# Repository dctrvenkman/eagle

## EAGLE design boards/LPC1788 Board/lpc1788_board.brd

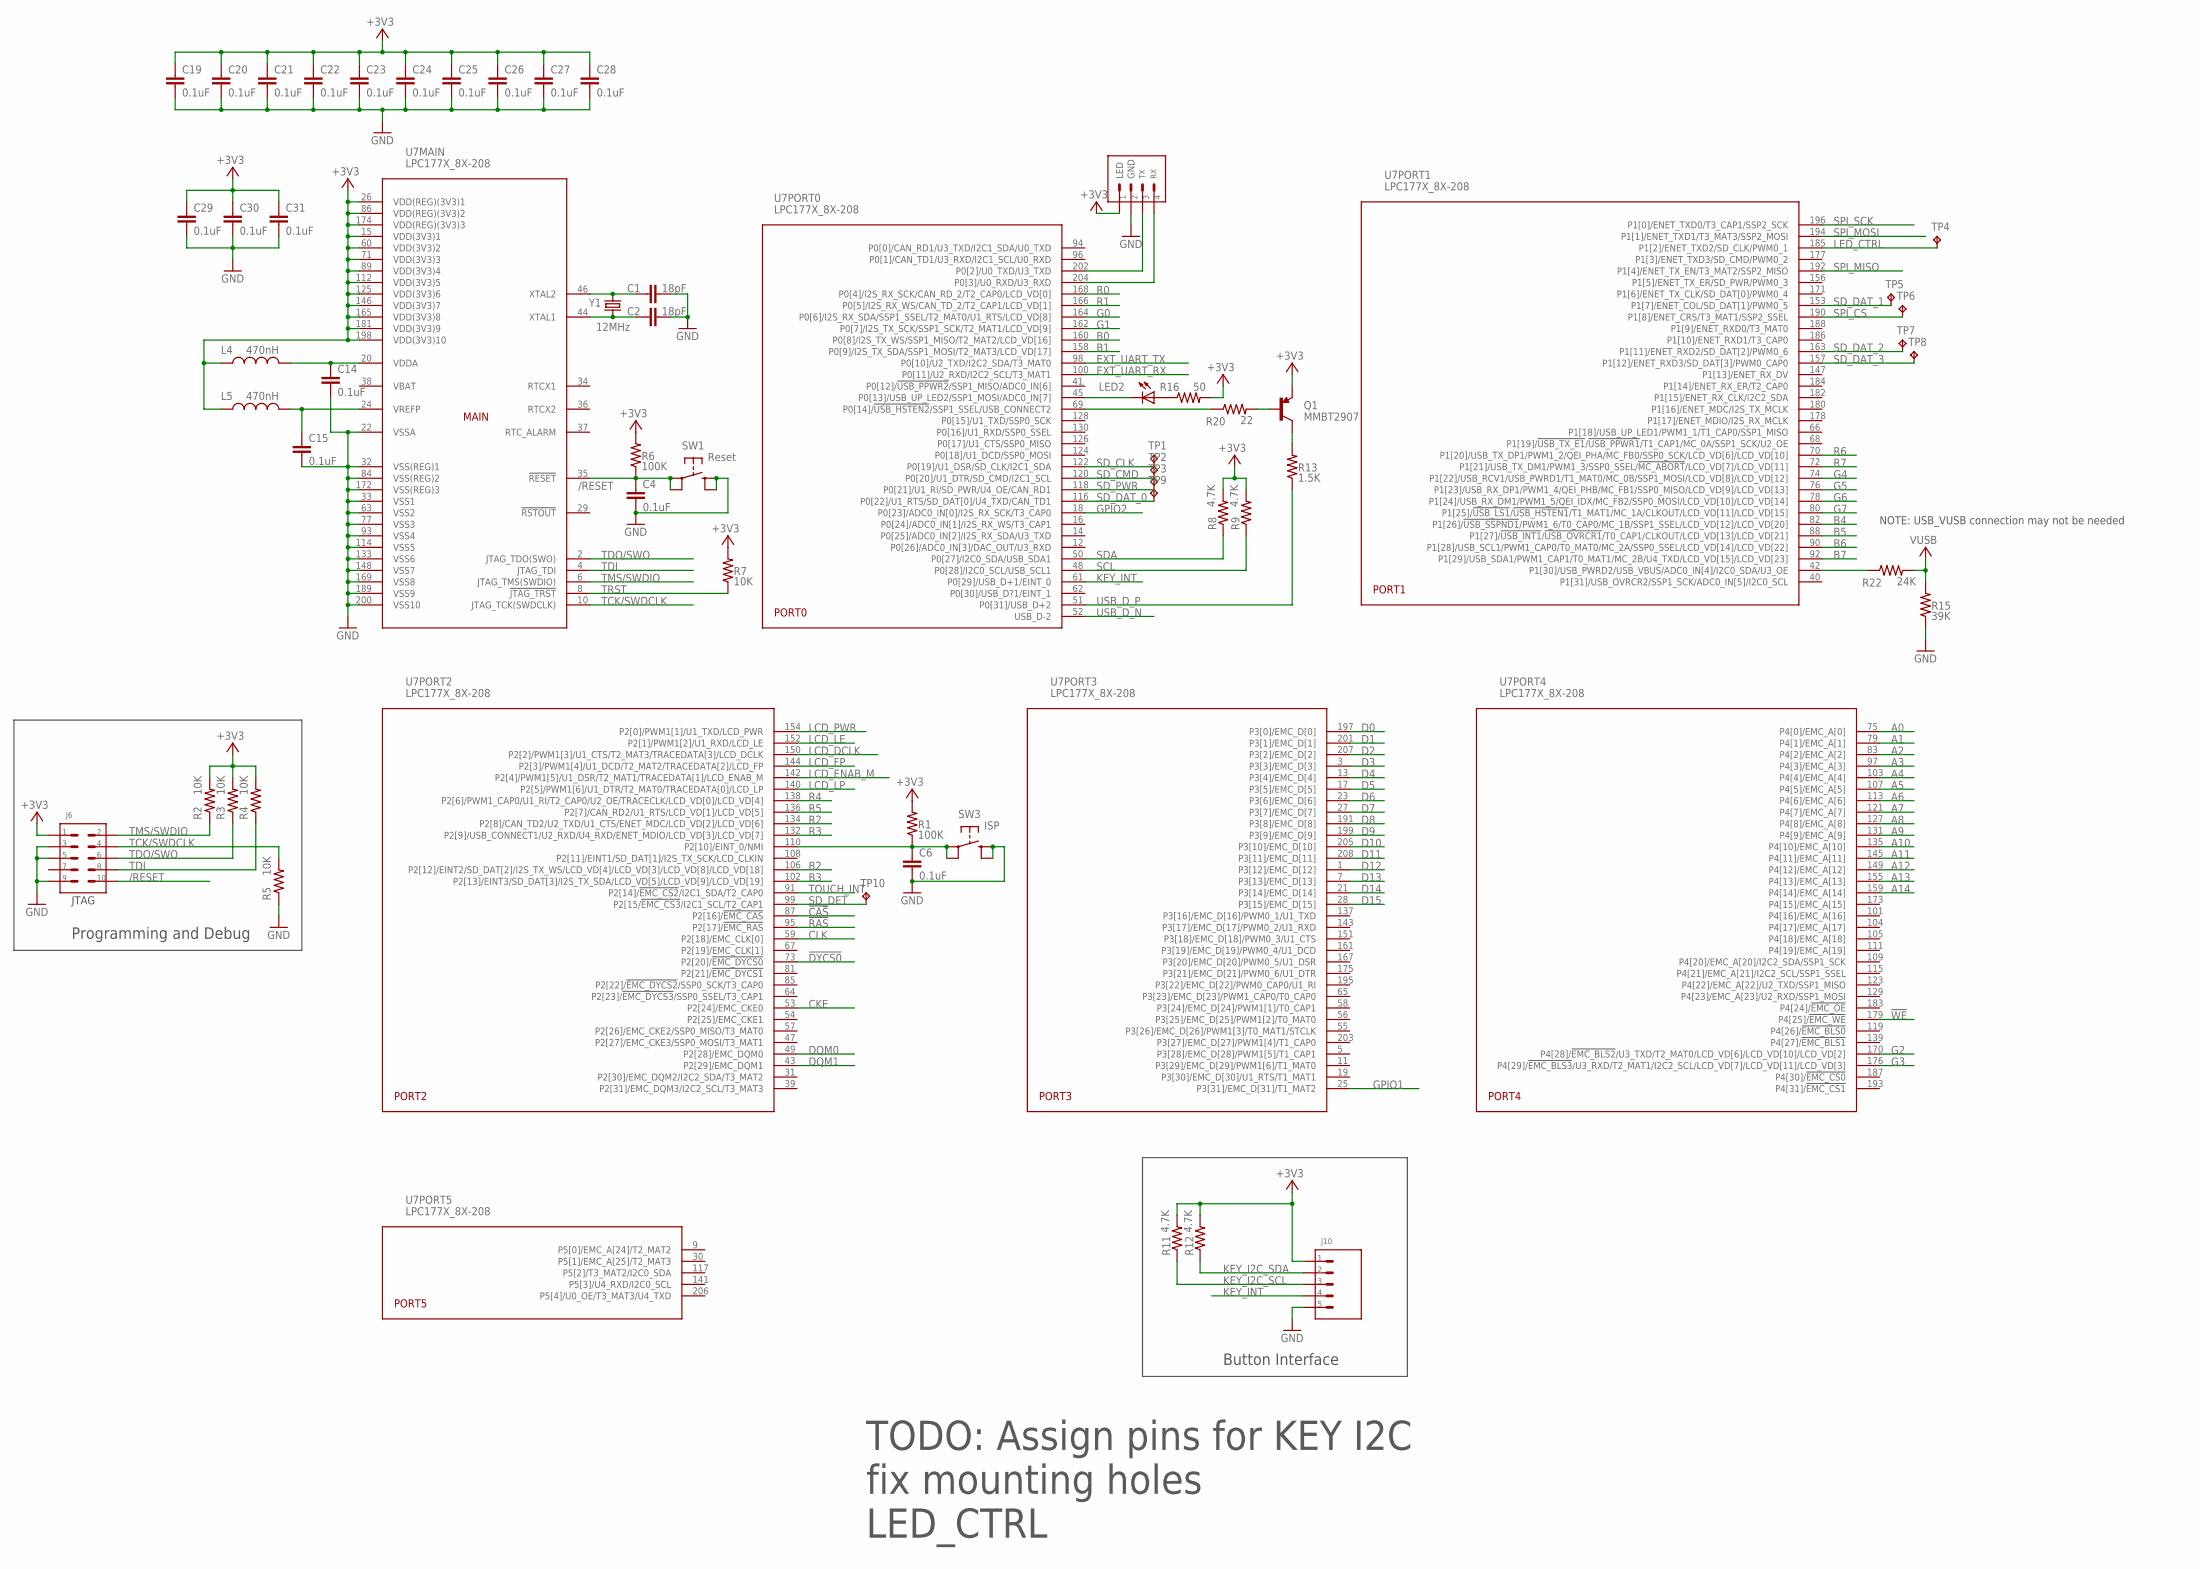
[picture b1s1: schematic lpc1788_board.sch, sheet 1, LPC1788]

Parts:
C1, C2: 18pF; C0402
C4, C6, C14, C15, C19, C20, C21, C22, C23, C24, C25, C26, C27, C28, C29, C30, C31: 0.1uF; C0402
J4: Console; 4-PIN_1.25MM
J6: JTAG; 10-PIN_5X2_.050IN_SMT
J10: MOLEX_527930570_5PIN_FFC_CONNECTOR; MOLEX_527930570
L4, L5: 470nH; 0603
LED2: USB; CHIPLED_0603
Q1: MMBT2907; SOT23
R1, R6: 100K; R0402
R2, R3, R4, R5, R7: 10K; R0402
R8, R9, R11, R12: 4.7K; R0402
R13: 1.5K; R0402
R15: 39K; R0402
R16: 50; R0402
R20: 22; R0402
R22: 24K; R0402
SW1: Reset; SMT_PUSHBUTTON
SW3: ISP; SMT_PUSHBUTTON
TP1, TP2, TP3, TP4, TP5, TP6, TP7, TP8, TP9, TP10: TPTP10R; TP10R
U7: LPC177X_8X-208; LQFP208
Y1: 12MHz; 2-SMD_8MMX4.5MM

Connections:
!CAS: U7.87 (P2[16]/!EMC_CAS!); also elsewhere on the board
!DYCS0: U7.73 (P2[20]/!EMC_DYCS0!); also elsewhere on the board
!RAS: U7.95 (P2[17]/!EMC_RAS!); also elsewhere on the board
!WE: U7.179 (P4[25]/!EMC_WE!); also elsewhere on the board
+3V3: C19.1, C20.1, C21.1, C22.1, C23.1, C24.1, C25.1, C26.1, C27.1, C28.1, C29.1, C30.1, C31.1, J4.1 (S1), J6.P$1 (S1), J10.P$1 (S1), L4.1, L5.1, Q1.2 (E), R1.2, R2.2, R3.2, R4.2, R6.2, R7.2, R8.2, R9.2, R11.2, R12.2, R16.2, U7.15 (VDD(3V3)1), U7.26 (VDD(REG)(3V3)1), U7.60 (VDD(3V3)2), U7.71 (VDD(3V3)3), U7.86 (VDD(REG)(3V3)2), U7.89 (VDD(3V3)4), U7.112 (VDD(3V3)5), U7.125 (VDD(3V3)6), U7.146 (VDD(3V3)7), U7.165 (VDD(3V3)8), U7.174 (VDD(REG)(3V3)3), U7.181 (VDD(3V3)9), U7.198 (VDD(3V3)10); also elsewhere on the board
+VUSB: R15.2, R22.2; also elsewhere on the board
/RESET: C4.1, J6.P$10 (S10), R6.1, SW1.P$1 (P1), SW1.P$2, U7.35 (!RESET!)
/RESET1: C6.1, R1.1, SW3.P$1 (P1), SW3.P$2, U7.110 (P2[10]/EINT_0/NMI)
A0: U7.75 (P4[0]/EMC_A[0]); also elsewhere on the board
A1: U7.79 (P4[1]/EMC_A[1]); also elsewhere on the board
A2: U7.83 (P4[2]/EMC_A[2]); also elsewhere on the board
A3: U7.97 (P4[3]/EMC_A[3]); also elsewhere on the board
A4: U7.103 (P4[4]/EMC_A[4]); also elsewhere on the board
A5: U7.107 (P4[5]/EMC_A[5]); also elsewhere on the board
A6: U7.113 (P4[6]/EMC_A[6]); also elsewhere on the board
A7: U7.121 (P4[7]/EMC_A[7]); also elsewhere on the board
A8: U7.127 (P4[8]/EMC_A[8]); also elsewhere on the board
A9: U7.131 (P4[9]/EMC_A[9]); also elsewhere on the board
A10: U7.135 (P4[10]/EMC_A[10]); also elsewhere on the board
A11: U7.145 (P4[11]/EMC_A[11]); also elsewhere on the board
A12: U7.149 (P4[12]/EMC_A[12]); also elsewhere on the board
A13: U7.155 (P4[13]/EMC_A[13]); also elsewhere on the board
A14: U7.159 (P4[14]/EMC_A[14]); also elsewhere on the board
B0: U7.160 (P0[8]/I2S_TX_WS/SSP1_MISO/T2_MAT2/LCD_V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); also elsewhere on the board
B1: U7.158 (P0[9]/I2S_TX_SDA/SSP1_MOSI/T2_MAT3/LCD_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); also elsewhere on the board
B2: U7.106 (P2[12]/EINT2/SD_DAT[2]/I2S_TX_WS/LCD_VD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); also elsewhere on the board
B3: U7.102 (P2[13]/EINT3/SD_DAT[3]/I2S_TX_SDA/LCD_V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); also elsewhere on the board
B4: U7.82 (P1[26]/!USB_SSPND1!/PWM1_6/T0_CAP0/MC_1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); also elsewhere on the board
B5: U7.88 (P1[27]/!USB_INT1!/!USB_OVRCR1!/T0_CAP1/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); also elsewhere on the board
B6: U7.90 (P1[28]/USB_SCL1/PWM1_CAP0/T0_MAT0/MC_2A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); also elsewhere on the board
B7: U7.92 (P1[29]/USB_SDA1/PWM1_CAP1/T0_MAT1/MC_2B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); also elsewhere on the board
CKE: U7.53 (P2[24]/EMC_CKE0); also elsewhere on the board
CLK: U7.59 (P2[18]/EMC_CLK[0]); also elsewhere on the board
D0: U7.197 (P3[0]/EMC_D[0]); also elsewhere on the board
D1: U7.201 (P3[1]/EMC_D[1]); also elsewhere on the board
D2: U7.207 (P3[2]/EMC_D[2]); also elsewhere on the board
D3: U7.3 (P3[3]/EMC_D[3]); also elsewhere on the board
D4: U7.13 (P3[4]/EMC_D[4]); also elsewhere on the board
D5: U7.17 (P3[5]/EMC_D[5]); also elsewhere on the board
D6: U7.23 (P3[6]/EMC_D[6]); also elsewhere on the board
D7: U7.27 (P3[7]/EMC_D[7]); also elsewhere on the board
D8: U7.191 (P3[8]/EMC_D[8]); also elsewhere on the board
D9: U7.199 (P3[9]/EMC_D[9]); also elsewhere on the board
D10: U7.205 (P3[10]/EMC_D[10]); also elsewhere on the board
D11: U7.208 (P3[11]/EMC_D[11]); also elsewhere on the board
D12: U7.1 (P3[12]/EMC_D[12]); also elsewhere on the board
D13: U7.7 (P3[13]/EMC_D[13]); also elsewhere on the board
D14: U7.21 (P3[14]/EMC_D[14]); also elsewhere on the board
D15: U7.28 (P3[15]/EMC_D[15]); also elsewhere on the board
DQM0: U7.49 (P2[28]/EMC_DQM0); also elsewhere on the board
DQM1: U7.43 (P2[29]/EMC_DQM1); also elsewhere on the board
EXT_UART_RX: U7.100 (P0[11]/U2_RXD/I2C2_SCL/T3_MAT1)
EXT_UART_TX: U7.98 (P0[10]/U2_TXD/I2C2_SDA/T3_MAT0)
G0: U7.164 (P0[6]/I2S_RX_SDA/SSP1_SSEL/T2_MAT0/U1_R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); also elsewhere on the board
G1: U7.162 (P0[7]/I2S_TX_SCK/SSP1_SCK/T2_MAT1/LCD_V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); also elsewhere on the board
G2: U7.170 (P4[28]/!EMC_BLS2!/U3_TXD/T2_MAT0/LCD_VD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); also elsewhere on the board
G3: U7.176 (P4[29]/!EMC_BLS3!/U3_RXD/T2_MAT1/I2C2_S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); also elsewhere on the board
G4: U7.74 (P1[22]/USB_RCV1/USB_PWRD1/T1_MAT0/MC_0B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); also elsewhere on the board
G5: U7.76 (P1[23]/USB_RX_DP1/PWM1_4/QEI_PHB/MC_FB1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); also elsewhere on the board
G6: U7.78 (P1[24]/USB_RX_DM1/PWM1_5/QEI_IDX/MC_FB2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); also elsewhere on the board
G7: U7.80 (P1[25]/!USB_LS1!/!USB_HSTEN1!/T1_MAT1/M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); also elsewhere on the board
GND: C1.2, C2.2, C4.2, C6.2, C14.2, C15.2, C19.2, C20.2, C21.2, C22.2, C23.2, C24.2, C25.2, C26.2, C27.2, C28.2, C29.2, C30.2, C31.2, J4.2 (S2), J6.P$3 (S3), J6.P$5 (S5), J6.P$9 (S9), J10.P$5 (S5), R5.1, R15.1, SW1.P$3 (S1), SW1.P$4 (S), SW3.P$3 (S1), SW3.P$4 (S), U7.22 (VSSA), U7.32 (VSS(REG)1), U7.33 (VSS1), U7.63 (VSS2), U7.77 (VSS3), U7.84 (VSS(REG)2), U7.93 (VSS4), U7.114 (VSS5), U7.133 (VSS6), U7.148 (VSS7), U7.169 (VSS8), U7.172 (VSS(REG)3), U7.189 (VSS9), U7.200 (VSS10); also elsewhere on the board
GPIO1: U7.25 (P3[31]/EMC_D[31]/T1_MAT2)
GPIO2: U7.18 (P0[23]/ADC0_IN[0]/I2S_RX_SCK/T3_CAP0)
KEY_I2C_SCL: J10.P$3 (S3), R11.1
KEY_I2C_SDA: J10.P$2 (S2), R12.1
KEY_INT: J10.P$4 (S4), U7.61 (P0[29]/USB_D+1/EINT_0)
LCD_DCLK: U7.150 (P2[2]/PWM1[3]/U1_CTS/T2_MAT3/TRACEDATA[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); also elsewhere on the board
LCD_ENAB_M: U7.142 (P2[4]/PWM1[5]/U1_DSR/T2_MAT1/TRACEDATA[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); also elsewhere on the board
LCD_FP: U7.144 (P2[3]/PWM1[4]/U1_DCD/T2_MAT2/TRACEDATA[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); also elsewhere on the board
LCD_LE: U7.152 (P2[1]/PWM1[2]/U1_RXD/LCD_LE); also elsewhere on the board
LCD_LP: U7.140 (P2[5]/PWM1[6]/U1_DTR/T2_MAT0/TRACEDATA[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); also elsewhere on the board
LCD_PWR: U7.154 (P2[0]/PWM1[1]/U1_TXD/LCD_PWR); also elsewhere on the board
LED_CTRL: TP4.TP, U7.185 (P1[2]/ENET_TXD2/SD_CLK/PWM0_1); also elsewhere on the board
unnamed: C1.1, U7.46 (XTAL2), Y1.2
unnamed: C2.1, U7.44 (XTAL1), Y1.1
unnamed: C14.1, L4.2, U7.20 (VDDA)
unnamed: C15.1, L5.2, U7.24 (VREFP)
unnamed: Q1.3 (C), R13.2
unnamed: R20.1, U7.69 (P0[14]/!USB_HSTEN2!/SSP1_SSEL/USB_CONNE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)
unnamed: LED2.A, R16.1
unnamed: LED2.C, U7.45 (P0[13]/USB_UP_LED2/SSP1_MOSI/ADC0_IN[7])
unnamed: J4.3 (S3), U7.202 (P0[2]/U0_TXD/U3_TXD)
unnamed: J4.4 (S4), U7.204 (P0[3]/U0_RXD/U3_RXD)
unnamed: Q1.1 (B), R20.2
unnamed: R22.1, U7.42 (P1[30]/USB_PWRD2/USB_VBUS/ADC0_IN[4]/I2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)
R0: U7.168 (P0[4]/I2S_RX_SCK/CAN_RD_2/T2_CAP0/LCD_V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); also elsewhere on the board
R1: U7.166 (P0[5]/I2S_RX_WS/CAN_TD_2/T2_CAP1/LCD_VD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); also elsewhere on the board
R2: U7.134 (P2[8]/CAN_TD2/U2_TXD/U1_CTS/ENET_MDC/LC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); also elsewhere on the board
R3: U7.132 (P2[9]/USB_CONNECT1/U2_RXD/U4_RXD/ENET_M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); also elsewhere on the board
R4: U7.138 (P2[6]/PWM1_CAP0/U1_RI/T2_CAP0/U2_OE/TRA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); also elsewhere on the board
R5: U7.136 (P2[7]/CAN_RD2/U1_RTS/LCD_VD[1]/LCD_VD[5]); also elsewhere on the board
R6: U7.70 (P1[20]/USB_TX_DP1/PWM1_2/QEI_PHA/MC_FB0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); also elsewhere on the board
R7: U7.72 (P1[21]/USB_TX_DM1/PWM1_3/SSP0_SSEL/!MC_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); also elsewhere on the board
SCL: R9.1, U7.48 (P0[28]/I2C0_SCL/USB_SCL1); also elsewhere on the board
SDA: R8.1, U7.50 (P0[27]/I2C0_SDA/USB_SDA1); also elsewhere on the board
SD_CLK: TP1.TP, U7.122 (P0[19]/U1_DSR/SD_CLK/I2C1_SDA); also elsewhere on the board
SD_CMD: TP2.TP, U7.120 (P0[20]/U1_DTR/SD_CMD/I2C1_SCL); also elsewhere on the board
SD_DAT_0: TP9.TP, U7.116 (P0[22]/U1_RTS/SD_DAT[0]/U4_TXD/CAN_TD1); also elsewhere on the board
SD_DAT_1: TP5.TP, U7.153 (P1[7]/ENET_COL/SD_DAT[1]/PWM0_5); also elsewhere on the board
SD_DAT_2: TP7.TP, U7.163 (P1[11]/ENET_RXD2/SD_DAT[2]/PWM0_6); also elsewhere on the board
SD_DAT_3: TP8.TP, U7.157 (P1[12]/ENET_RXD3/SD_DAT[3]/PWM0_CAP0); also elsewhere on the board
SD_DET: U7.99 (P2[15/!EMC_CS3!/I2C1_SCL/T2_CAP1); also elsewhere on the board
SD_PWR: TP3.TP, U7.118 (P0[21]/U1_RI/SD_PWR/U4_OE/CAN_RD1); also elsewhere on the board
SPI_CS: TP6.TP, U7.190 (P1[8]/ENET_CRS/T3_MAT1/SSP2_SSEL)
SPI_MISO: U7.192 (P1[4]/ENET_TX_EN/T3_MAT2/SSP2_MISO)
SPI_MOSI: U7.194 (P1[1]/ENET_TXD1/T3_MAT3/SSP2_MOSI)
SPI_SCK: U7.196 (P1[0]/ENET_TXD0/T3_CAP1/SSP2_SCK)
TCK/SWDCLK: J6.P$4 (S4), R5.2, U7.10 (JTAG_TCK(SWDCLK))
TDI: J6.P$8 (S8), R4.1, U7.4 (JTAG_TDI)
TDO/SWO: J6.P$6 (S6), R3.1, U7.2 (JTAG_TDO(SWO))
TMS/SWDIO: J6.P$2 (S2), R2.1, U7.6 (JTAG_TMS(SWDIO))
TOUCH_INT: U7.91 (P2[14]/!EMC_CS2!/I2C1_SDA/T2_CAP0); also elsewhere on the board
TRST: R7.1, U7.8 (!JTAG_TRST!)
USB_D_N: U7.52 (USB_D-2); also elsewhere on the board
USB_D_P: R13.1, U7.51 (P0[31]/USB_D+2); also elsewhere on the board

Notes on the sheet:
JTAG
Programming and Debug
Button Interface
NOTE: USB_VUSB connection may not be needed
TODO: Assign pins for KEY I2C fix mounting holes LED_CTRL

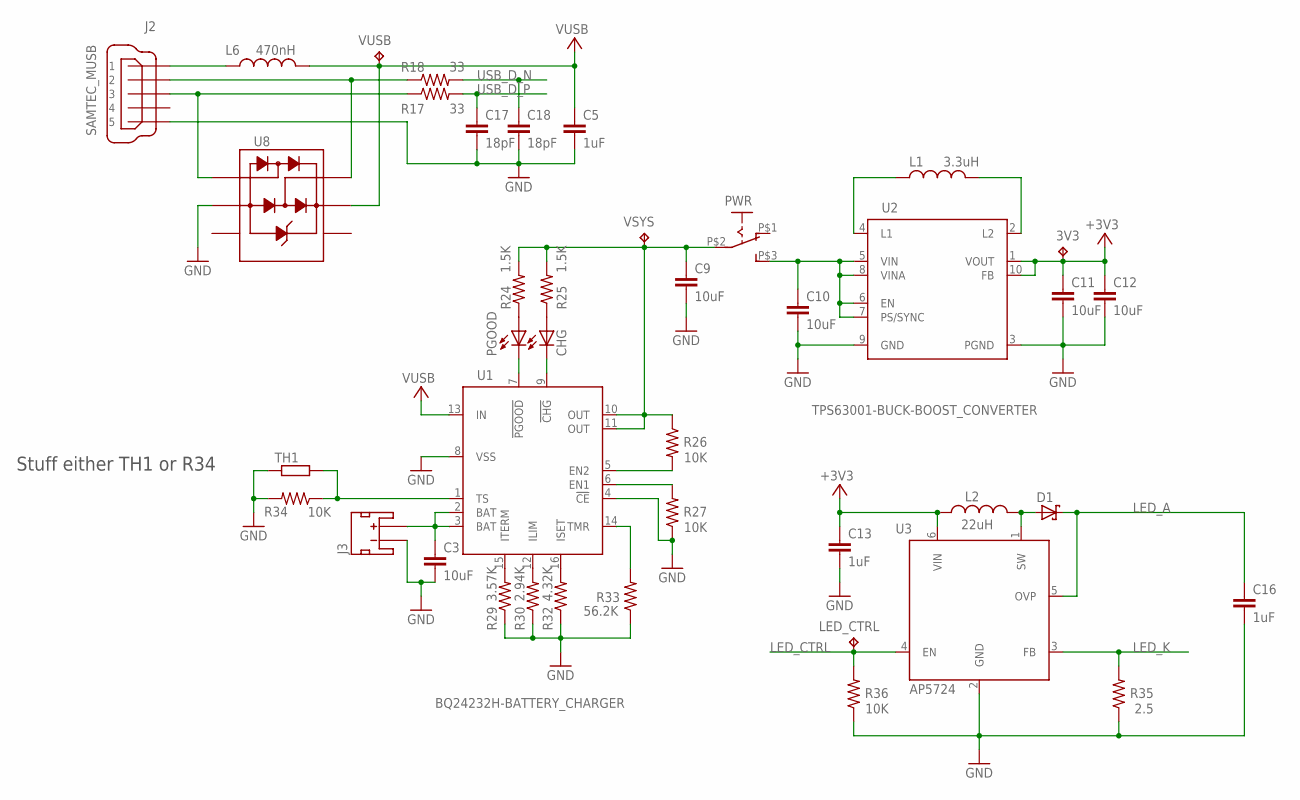
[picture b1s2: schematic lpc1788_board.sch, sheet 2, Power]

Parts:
3V3: TPTP10R; TP10R
C3, C9, C10, C11, C12: 10uF; C0805K
C5, C13, C16: 1uF; C0402
C17, C18: 18pF; C0402
CHG: USB; CHIPLED_0603
D1: B0540WS-SCHOTTKY_DIODE; SOD-323
J2: SAMTEC_MUSB; MUSB-05-X-B-SM-A
J3: JST_2MM_SMT
L1: 3.3uH; 3015
L2: 22uH; 4012
L6: 470nH; 0603
LED_CTRL: TPTP10R; TP10R
PGOOD: USB; CHIPLED_0603
PWR: OS102011MA1QS1
R17, R18: 33; R0402
R24, R25: 1.5K; R0402
R26, R27, R34, R36: 10K; R0402
R29: 3.57K; R0402
R30: 2.94K; R0402
R32: 4.32K; R0402
R33: 56.2K; R0402
R35: 2.5; R0402
TH1: R-EU_0204/2V; 0204V
U1: BQ24232H-BATTERY_CHARGER; QFN-16
U2: TPS63001-BUCK-BOOST_CONVERTER; QFN-10
U3: AP5724; SOT-26
U8: NUP2202; SC-88
VSYS: TPTP10R; TP10R
VUSB: TPTP10R; TP10R

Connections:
+3V3: 3V3.TP, C11.1, C12.1, C13.1, L2.1, U2.1 (VOUT), U2.10 (FB), U3.6 (VIN); also elsewhere on the board
+VUSB: C5.1, L6.2, U1.13 (IN), U8.P$5, VUSB.TP; also elsewhere on the board
D_N: J2.2, R18.1, U8.P$6
D_P: J2.3, R17.1, U8.P$1
GND: C3.2, C5.2, C9.2, C10.2, C11.2, C12.2, C13.2, C16.2, C17.2, C18.2, J2.5, J3.1 (-), R27.1, R29.1, R30.1, R32.1, R33.1, R34.2, R35.1, R36.1, TH1.1, U1.4 (!CE), U1.8 (VSS), U2.3 (PGND), U2.9 (GND), U3.2 (GND), U8.P$2; also elsewhere on the board
LED_A: C16.1, D1.C, U3.5 (OVP); also elsewhere on the board
LED_CTRL: LED_CTRL.TP, R36.2, U3.4 (EN); also elsewhere on the board
LED_K: R35.2, U3.3 (FB); also elsewhere on the board
unnamed: C9.1, PWR.P$2, R24.2, R25.2, R26.1, U1.10 (OUT), U1.11 (OUT), VSYS.TP
unnamed: R26.2, U1.5 (EN2)
unnamed: R27.2, U1.6 (EN1)
unnamed: PGOOD.A, R24.1
unnamed: CHG.A, R25.1
unnamed: PGOOD.C, U1.7 (!PGOOD)
unnamed: CHG.C, U1.9 (!CHG)
unnamed: C3.1, J3.2 (+), U1.2 (BAT), U1.3 (BAT)
unnamed: R34.1, TH1.2, U1.1 (TS)
unnamed: R29.2, U1.15 (ITERM)
unnamed: R30.2, U1.12 (ILIM)
unnamed: R32.2, U1.16 (ISET)
unnamed: C10.1, PWR.P$3 (S), U2.5 (VIN), U2.6 (EN), U2.7 (PS/SYNC), U2.8 (VINA)
unnamed: R33.2, U1.14 (TMR)
unnamed: L1.1, U2.4 (L1)
unnamed: L1.2, U2.2 (L2)
unnamed: D1.A, L2.2, U3.1 (SW)
unnamed: J2.1, L6.1
USB_D_N: C18.1, R18.2; also elsewhere on the board
USB_D_P: C17.1, R17.2; also elsewhere on the board

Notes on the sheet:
Stuff either TH1 or R34

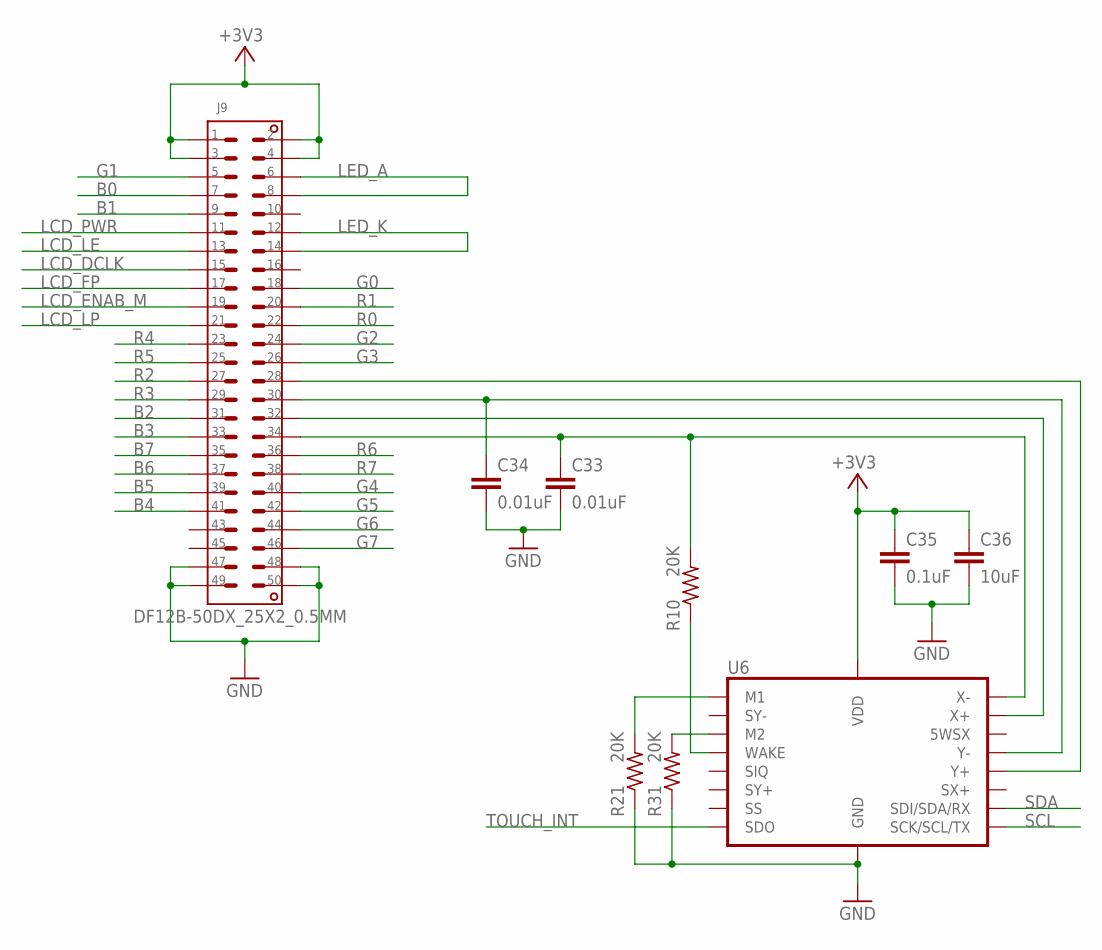
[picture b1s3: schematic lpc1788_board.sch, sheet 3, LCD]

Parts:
C33, C34: 0.01uF; C0402
C35: 0.1uF; C0402
C36: 10uF; C0402
J9: DF12B-50DX_25X2_0.5MM
R10, R21, R31: 20K; R0402
U6: AR1021-RESISTIVE_TOUCH_CONTROLLER; SSOP-20

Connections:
+3V3: C35.1, C36.1, J9.P$1 (S1), J9.P$2 (S2), J9.P$3 (S3), J9.P$4 (S4), U6.P$1 (VDD); also elsewhere on the board
B0: J9.P$7 (S7); also elsewhere on the board
B1: J9.P$9 (S9); also elsewhere on the board
B2: J9.P$31 (S31); also elsewhere on the board
B3: J9.P$33 (S33); also elsewhere on the board
B4: J9.P$41 (S41); also elsewhere on the board
B5: J9.P$39 (S39); also elsewhere on the board
B6: J9.P$37 (S37); also elsewhere on the board
B7: J9.P$35 (S35); also elsewhere on the board
G0: J9.P$18 (S18); also elsewhere on the board
G1: J9.P$5 (S5); also elsewhere on the board
G2: J9.P$24 (S24); also elsewhere on the board
G3: J9.P$26 (S26); also elsewhere on the board
G4: J9.P$40 (S40); also elsewhere on the board
G5: J9.P$42 (S42); also elsewhere on the board
G6: J9.P$44 (S44); also elsewhere on the board
G7: J9.P$46 (S46); also elsewhere on the board
GND: C33.2, C34.2, C35.2, C36.2, J9.P$47 (S47), J9.P$48 (S48), J9.P$49 (S49), J9.P$50 (S50), R21.1, R31.1, U6.P$20 (GND); also elsewhere on the board
LCD_DCLK: J9.P$15 (S15); also elsewhere on the board
LCD_ENAB_M: J9.P$19 (S19); also elsewhere on the board
LCD_FP: J9.P$17 (S17); also elsewhere on the board
LCD_LE: J9.P$13 (S13); also elsewhere on the board
LCD_LP: J9.P$21 (S21); also elsewhere on the board
LCD_PWR: J9.P$11 (S11); also elsewhere on the board
LED_A: J9.P$6 (S6), J9.P$8 (S8); also elsewhere on the board
LED_K: J9.P$12 (S12), J9.P$14 (S14); also elsewhere on the board
unnamed: C33.1, J9.P$34 (S34), R10.2, U6.P$19 (X-)
unnamed: J9.P$32 (S32), U6.P$18 (X+)
unnamed: C34.1, J9.P$30 (S30), U6.P$16 (Y-)
unnamed: J9.P$28 (S28), U6.P$15 (Y+)
unnamed: R21.2, U6.P$2 (M1)
unnamed: R10.1, U6.P$5 (WAKE)
unnamed: R31.2, U6.P$4 (M2)
R0: J9.P$22 (S22); also elsewhere on the board
R1: J9.P$20 (S20); also elsewhere on the board
R2: J9.P$27 (S27); also elsewhere on the board
R3: J9.P$29 (S29); also elsewhere on the board
R4: J9.P$23 (S23); also elsewhere on the board
R5: J9.P$25 (S25); also elsewhere on the board
R6: J9.P$36 (S36); also elsewhere on the board
R7: J9.P$38 (S38); also elsewhere on the board
SCL: U6.P$11 (SCK/SCL/TX); also elsewhere on the board
SDA: U6.P$13 (SDI/SDA/RX); also elsewhere on the board
TOUCH_INT: U6.P$9 (SDO); also elsewhere on the board

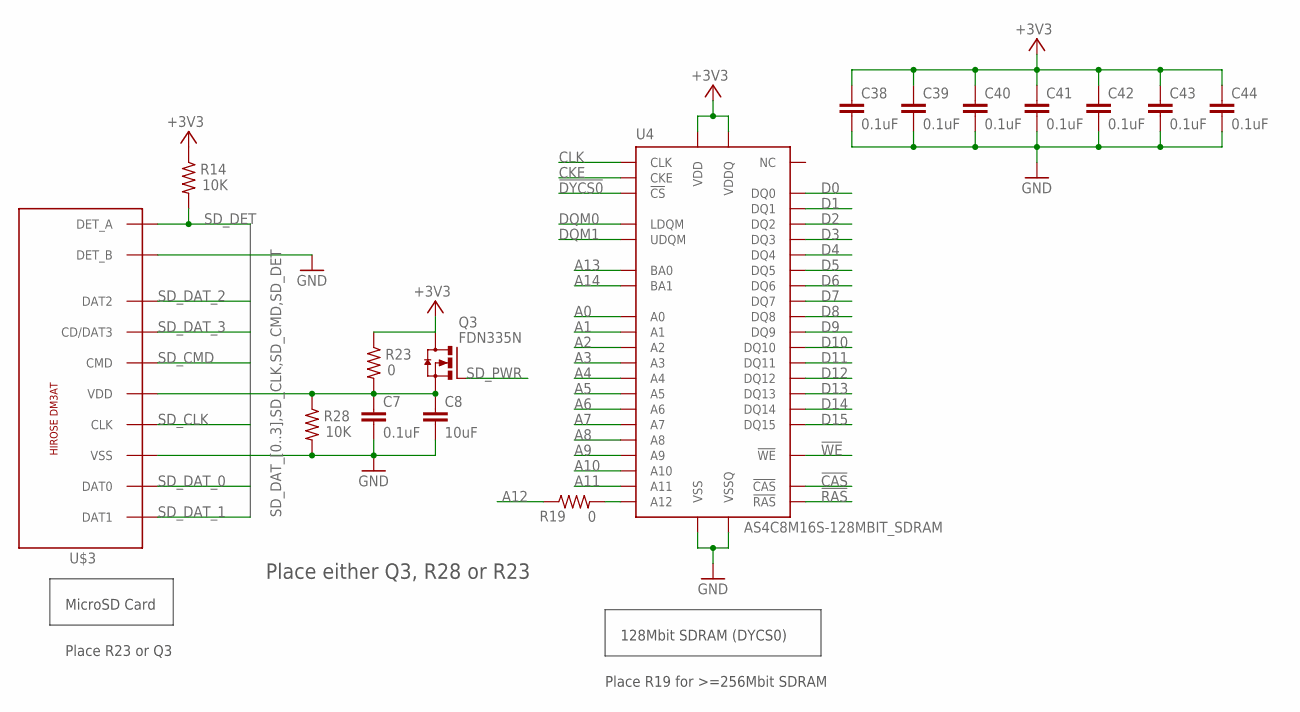
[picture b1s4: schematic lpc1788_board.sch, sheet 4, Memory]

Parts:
C7, C38, C39, C40, C41, C42, C43, C44: 0.1uF; C0402
C8: 10uF; C0805K
Q3: FDN335N; SUPER-SOT3
R14, R28: 10K; R0402
R19, R23: 0; R0402
U4: AS4C8M16S-128MBIT_SDRAM; TSOP54-II
U$3: DM3AT

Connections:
!CAS: U4.P$17 (!CAS); also elsewhere on the board
!DYCS0: U4.P$19 (!CS); also elsewhere on the board
!RAS: U4.P$18 (!RAS); also elsewhere on the board
!WE: U4.P$16 (!WE); also elsewhere on the board
+3V3: C38.1, C39.1, C40.1, C41.1, C42.1, C43.1, C44.1, Q3.3 (D), R14.1, R23.1, U4.P$1 (VDD), U4.P$3 (VDDQ), U4.P$9 (VDDQ), U4.P$14 (VDD), U4.P$27 (VDD), U4.P$43 (VDDQ), U4.P$49 (VDDQ); also elsewhere on the board
A0: U4.P$23 (A0); also elsewhere on the board
A1: U4.P$24 (A1); also elsewhere on the board
A2: U4.P$25 (A2); also elsewhere on the board
A3: U4.P$26 (A3); also elsewhere on the board
A4: U4.P$29 (A4); also elsewhere on the board
A5: U4.P$30 (A5); also elsewhere on the board
A6: U4.P$31 (A6); also elsewhere on the board
A7: U4.P$32 (A7); also elsewhere on the board
A8: U4.P$33 (A8); also elsewhere on the board
A9: U4.P$34 (A9); also elsewhere on the board
A10: U4.P$22 (A10); also elsewhere on the board
A11: U4.P$35 (A11); also elsewhere on the board
A12: R19.1; also elsewhere on the board
A13: U4.P$20 (BA0); also elsewhere on the board
A14: U4.P$21 (BA1); also elsewhere on the board
CKE: U4.P$37 (CKE); also elsewhere on the board
CLK: U4.P$38 (CLK); also elsewhere on the board
D0: U4.P$2 (DQ0); also elsewhere on the board
D1: U4.P$4 (DQ1); also elsewhere on the board
D2: U4.P$5 (DQ2); also elsewhere on the board
D3: U4.P$7 (DQ3); also elsewhere on the board
D4: U4.P$8 (DQ4); also elsewhere on the board
D5: U4.P$10 (DQ5); also elsewhere on the board
D6: U4.P$11 (DQ6); also elsewhere on the board
D7: U4.P$13 (DQ7); also elsewhere on the board
D8: U4.P$42 (DQ8); also elsewhere on the board
D9: U4.P$44 (DQ9); also elsewhere on the board
D10: U4.P$45 (DQ10); also elsewhere on the board
D11: U4.P$47 (DQ11); also elsewhere on the board
D12: U4.P$48 (DQ12); also elsewhere on the board
D13: U4.P$50 (DQ13); also elsewhere on the board
D14: U4.P$51 (DQ14); also elsewhere on the board
D15: U4.P$53 (DQ15); also elsewhere on the board
DQM0: U4.P$15 (LDQM); also elsewhere on the board
DQM1: U4.P$39 (UDQM); also elsewhere on the board
GND: C7.2, C8.2, C38.2, C39.2, C40.2, C41.2, C42.2, C43.2, C44.2, R28.2, U4.P$6 (VSSQ), U4.P$12 (VSSQ), U4.P$28 (VSS), U4.P$41 (VSS), U4.P$46 (VSSQ), U4.P$52 (VSSQ), U4.P$54 (VSS), U$3.DET_B, U$3.VSS; also elsewhere on the board
unnamed: C7.1, C8.1, Q3.2 (S), R23.2, R28.1, U$3.VDD
unnamed: R19.2, U4.P$36 (A12)
SD_CLK: U$3.CLK; also elsewhere on the board
SD_CMD: U$3.CMD; also elsewhere on the board
SD_DAT_0: U$3.DAT0; also elsewhere on the board
SD_DAT_1: U$3.DAT1; also elsewhere on the board
SD_DAT_2: U$3.DAT2; also elsewhere on the board
SD_DAT_3: U$3.CD/DAT3; also elsewhere on the board
SD_DET: R14.2, U$3.DET_A; also elsewhere on the board
SD_PWR: Q3.1 (G); also elsewhere on the board

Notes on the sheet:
128Mbit SDRAM (DYCS0)
MicroSD Card
Place R19 for >=256Mbit SDRAM
Place R23 or Q3
Place either Q3, R28 or R23

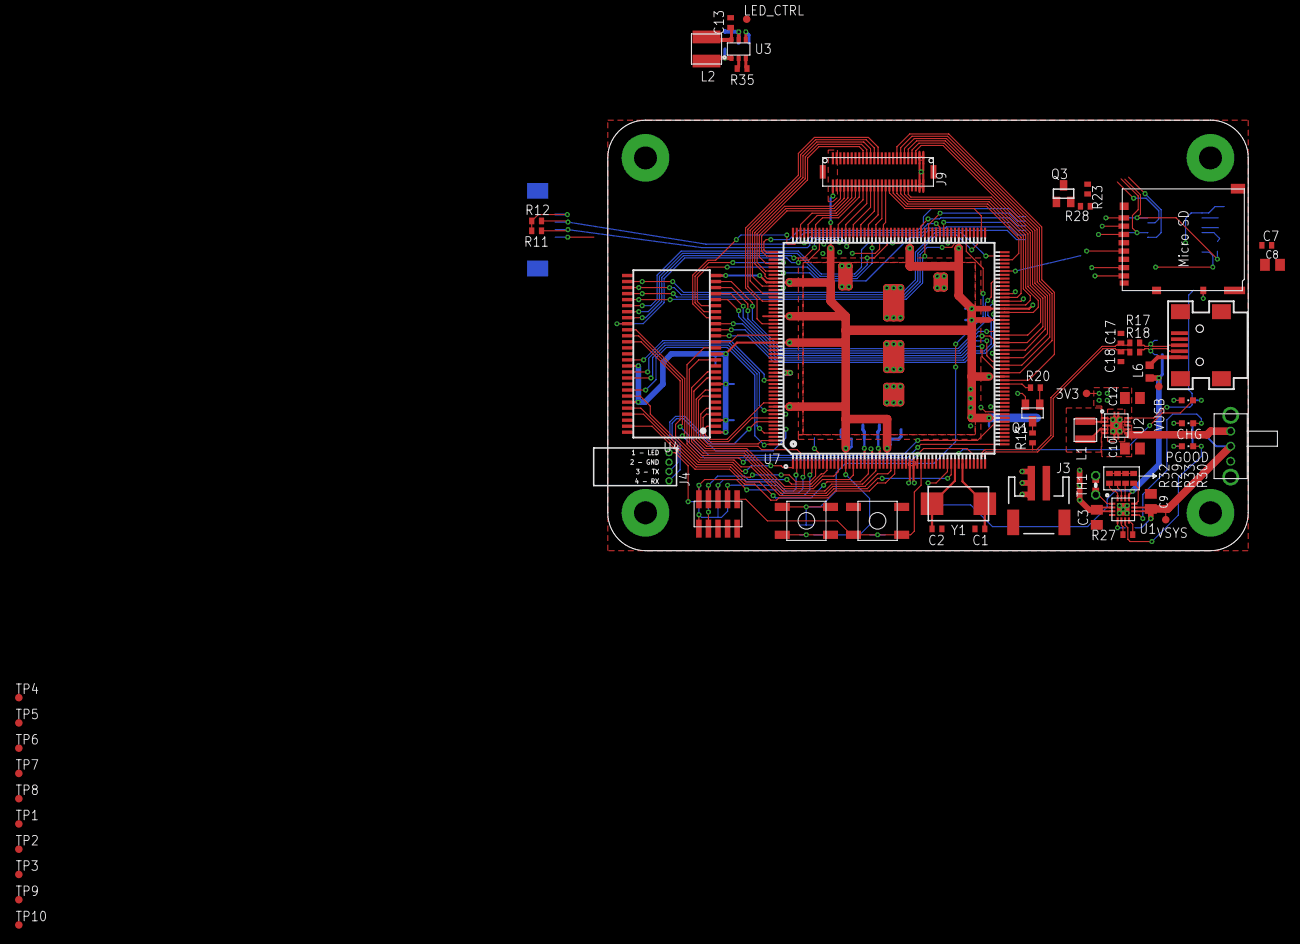
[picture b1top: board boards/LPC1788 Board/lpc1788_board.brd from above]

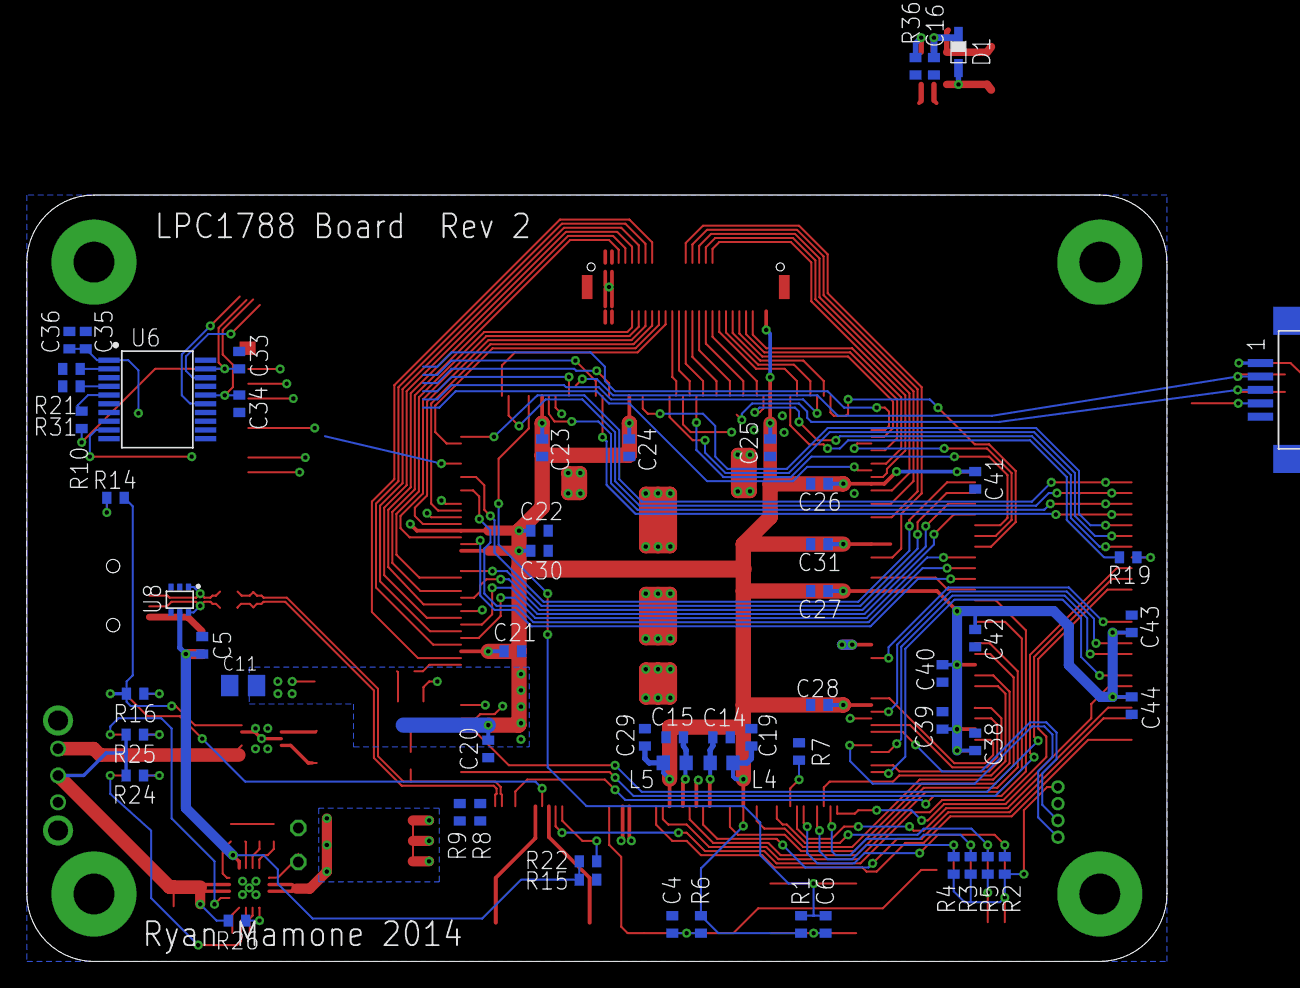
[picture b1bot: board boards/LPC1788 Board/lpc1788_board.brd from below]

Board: 2 copper layers, 85.0 x 57.1 mm, 122 parts (58 on the bottom side), 140 nets.

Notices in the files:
parts and their libraries:
SparkFun-DiscreteSemi: Licensing: CC v3.0 Share-Alike You are welcome to use this library for commercial purposes.
